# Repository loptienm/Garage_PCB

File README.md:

Garage_PCB
==========

This is a Garage Controller that will be able to open/close the garage door, tell me when to stop pulling forward, and read garage door open/close status.  The controller will run on a Spark Core and will use a supersonic range finder to get the distance from the wall to the car bumper to tell me when to stop pulling forward, it will use a reed switch to tell if the garage door is open or not, and it will be able to interface with the garage door opener without changing any of the existing hardware.

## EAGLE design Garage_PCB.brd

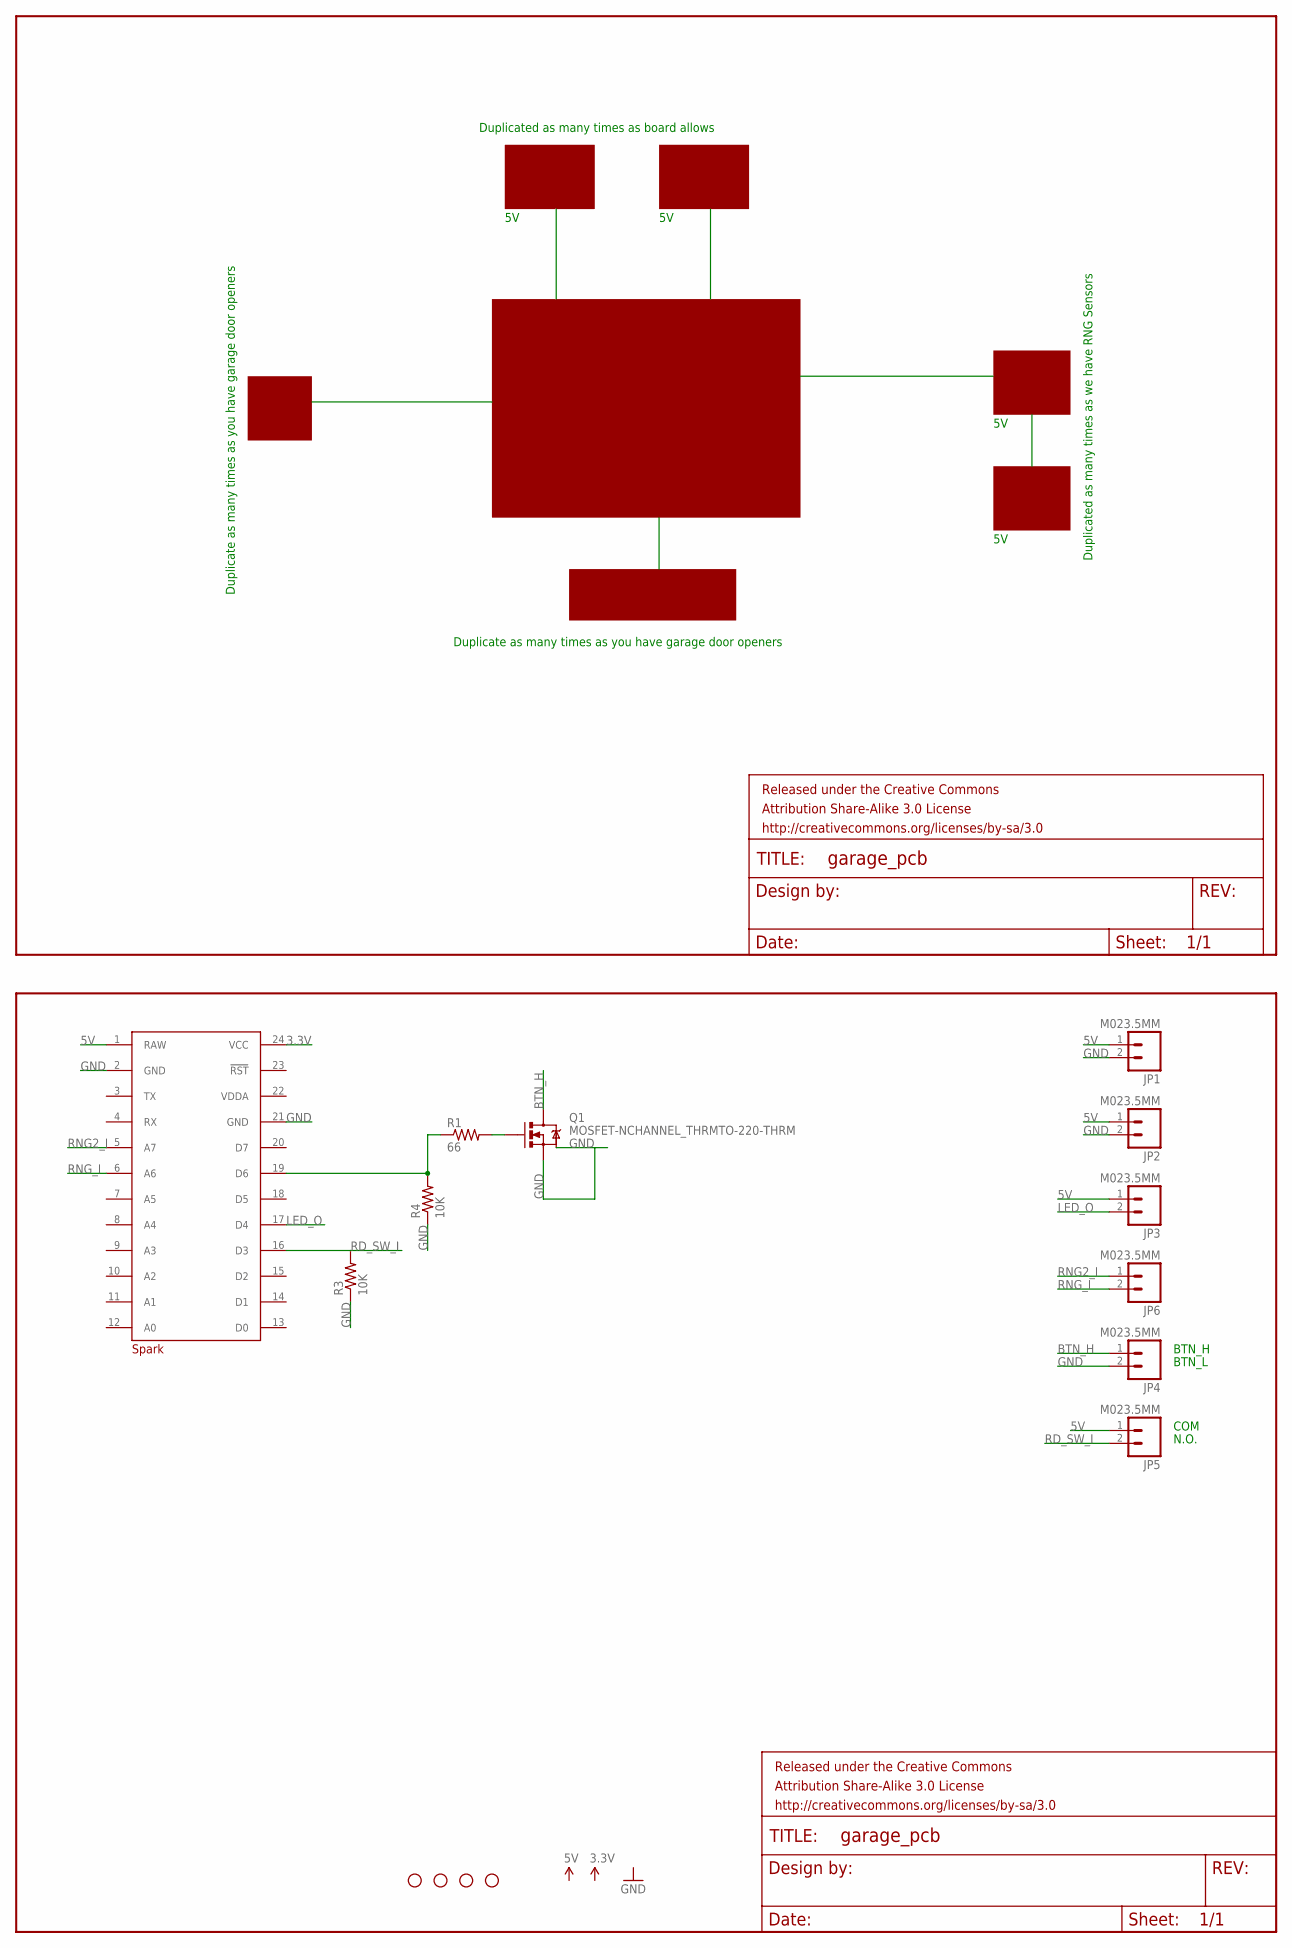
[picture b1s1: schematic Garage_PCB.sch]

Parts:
FRAME1, FRAME2: FRAME-LETTER; CREATIVE_COMMONS
JP1, JP2, JP3, JP4, JP5, JP6: M023.5MM; SCREWTERMINAL-3.5MM-2
Q1: MOSFET-NCHANNEL_THRMTO-220-THRM; TO220-THRM
R1: 66; 0603-RES
R3, R4: 10K; 0603-RES
SPARK: SPARK_CORECORE; SPARK_CORE
STANDOFF1, STANDOFF2, STANDOFF3, STANDOFF4: STAND-OFF
U$2: SPARK_LOGO2

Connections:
3.3V: SPARK.24 (VCC)
5V: JP1.1, JP2.1, JP3.1, JP5.1, SPARK.1 (RAW)
BTN_H: JP4.1, Q1.GND (D)
GND: JP1.2, JP2.2, JP4.2, Q1.OUT (S), Q1.THRM, R3.1, R4.1, SPARK.2 (GND), SPARK.21 (GND)
LED_O: JP3.2, SPARK.17 (D4)
unnamed: R1.1, R4.2, SPARK.19 (D6)
unnamed: Q1.IN (G), R1.2
RD_SW_I: JP5.2, R3.2, SPARK.16 (D3)
RNG2_I: JP6.1, SPARK.5 (A7)
RNG_I: JP6.2, SPARK.6 (A6)
VDDA: SPARK.22 (VDDA)

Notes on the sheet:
N.O.
COM
Duplicated as many times as board allows
Duplicated as many times as we have RNG Sensors
Duplicate as many times as you have garage door openers
BTN_L
BTN_H

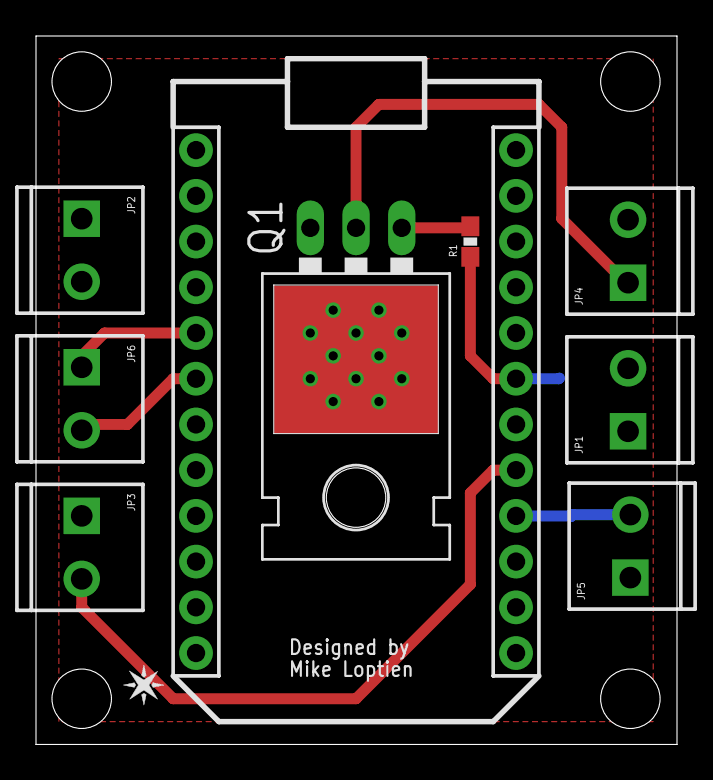
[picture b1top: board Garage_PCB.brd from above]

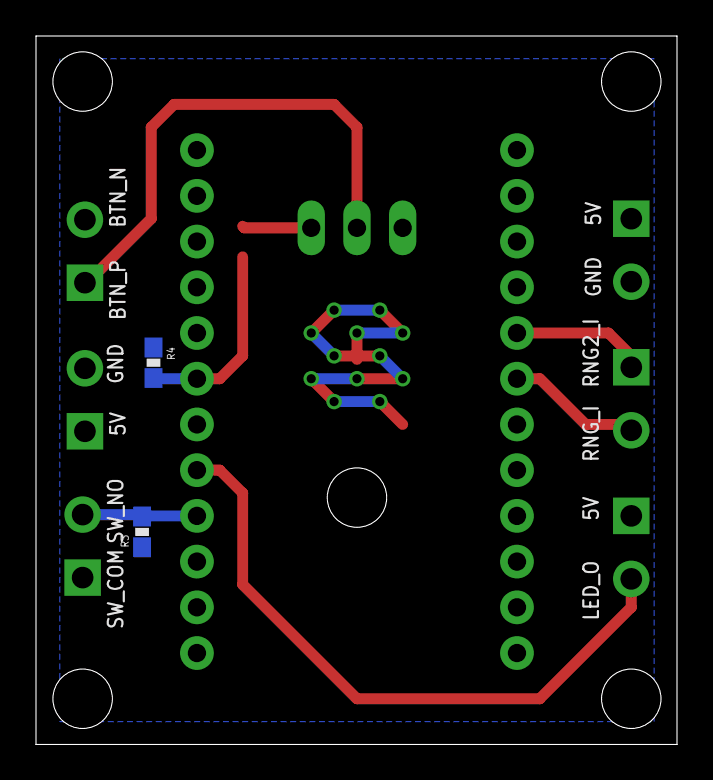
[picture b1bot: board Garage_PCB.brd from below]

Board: 2 copper layers, 35.6 x 39.4 mm, 18 parts (2 on the bottom side), 9 nets.

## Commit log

2014-04-16 Initial commit of git stuff
    Just the git stuff required for github.
2014-04-16 Add README.md
2014-04-16 Add initial Eagle schematic
    Add an Eagle Schematic and project file. The schematic just has a
    border and some power rails (5V, 3.3V, GND).
2014-04-20 Added parts, created board, placed parts and rails
    Added Spark core, 5V regulator, N-channel MOSFET for switching the 24V
    line for the garage door, and some screw terminals that I can connect to
    the Magnetic switch
    (http://www.amazon.com/Directed-Electronics-8601-Magnetic-Switch/dp/B0009SUF08/ref=sr_1_2?ie=UTF8&qid=1397978783&sr=8-2&keywords=reed+switch),
    a range finder (https://www.sparkfun.com/products/8503), and an RGB LED
    (https://www.sparkfun.com/products/11820). These parts will allow me to
2014-04-20 Routed the traces
    Routed all the traces for the board. Ran a DRC and there were no
    errors.
2014-04-20 Changed screw terminals to 3.5mm pitch instead of 2.54mm
    These screw terminals are much less ugly but are a bit bigger. They
    still fit pretty well though.
2014-04-20 Put 5V regulator on top layer
    Moved the regulator from the bottom layer to the top layer. It is still
    underneath the Spark but there should be plenty of room for it.
2014-04-20 Added my name and the Spark logo
    Added my name to the board and the Spark logo as well. Also added the
    Spark Eagle Library to the Eagle directory search paths so that I can
    edit library parts.
2014-04-20 Moved Mosfet and shrunk design
    Moved the MOSFET underneath the Spark on the bottom layer so I can save
    some space. I moved just about everything around and was able to shrink
    the board down to basically just the size of the Spark and the extra
    width of the screw terminals. It is very small now and costs almost $4
    less to build.
2014-06-14 Moved the Mosfet to top layer
    Moved the Mosfet to the top layer and made the necessary changes to the
    board to connect it. Also moved one of the Range finder pins to be
    closer to the other. Added a thermal pad to the Mosfet and added some
    thermal vias.
2014-06-15 Added a pulldown to the BTN_L side
    After some breadboard testing I found that the low side of the garage
    door button needs to be pulled down to ground in order to de-energize
    the line so that a new contact successfully gets registered. Added this
    pulldown and ordered this revision of the board.
2014-07-04 Removed MOSFET inline resistors
    The garage door button needs to have a direct connection from power
    (btn_h) to ground (btn_l) in order to open or close the garage door.
    The high side resistor kept this from happening. I am not sure what I
    was thinking with the low side 'pull down'. This was just a weird
    resistor connecting a groundplane on the opener to a ground plane on my
    board.

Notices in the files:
parts and their libraries:
SparkFun-Aesthetics: Licensing: CC v3.0 Share-Alike You are welcome to use this library for commercial purposes.
SparkFun-Aesthetics: Released under the Creative Commons Attribution Share-Alike 3.0 License
SparkFun-Aesthetics: http://creativecommons.org/licenses/by-sa/3.0
